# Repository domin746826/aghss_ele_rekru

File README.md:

# aghss_ele_rekru
rekrutacja do ele 2024

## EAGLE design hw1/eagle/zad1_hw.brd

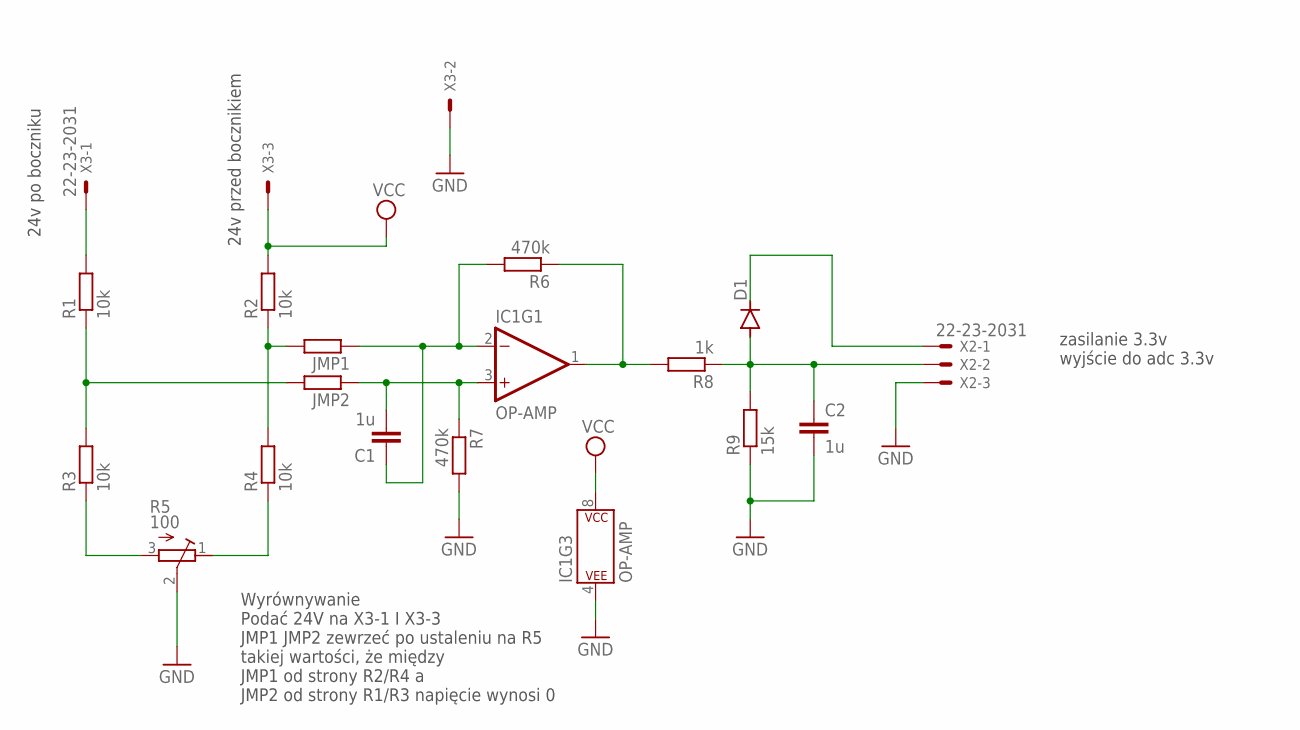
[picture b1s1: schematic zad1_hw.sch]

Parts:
C1, C2: 1u; C1206
D1: DIODE-DO214AC; DO214AC
IC1: OP-AMP; SO08
JMP1, JMP2: 0; R1206
R1, R2, R3, R4: 10k; R1206
R5: 100; RTRIMT93YA
R6, R7: 470k; R1206
R8: 1k; R1206
R9: 15k; R1206
X2, X3: 22-23-2031

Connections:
GND: C2.2, IC1.4 (P$V-), R5.2 (S), R7.2, R9.1, X2.3, X3.2
unnamed: R3.1, R5.3 (A)
unnamed: R4.1, R5.1 (E)
unnamed: JMP1.2, R2.1, R4.2
unnamed: JMP2.2, R1.1, R3.2
unnamed: R1.2, X3.1
unnamed: D1.C, X2.1
unnamed: C1.1, IC1.2 (-IN), JMP1.1, R6.2
unnamed: C1.2, IC1.3 (+IN), JMP2.1, R7.1
unnamed: IC1.1 (OUT), R6.1, R8.2
unnamed: C2.1, D1.A, R8.1, R9.2, X2.2
VCC: IC1.8 (P$V+), R2.2, X3.3

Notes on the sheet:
24v przed bocznikiem
24v po boczniku
zasilanie 3.3v wyjście do adc 3.3v
Wyrównywanie Podać 24V na X3-1 I X3-3 JMP1 JMP2 zewrzeć po ustaleniu na R5 takiej wartości, że między JMP1 od strony R2/R4 a JMP2 od strony R1/R3 napięcie wynosi 0

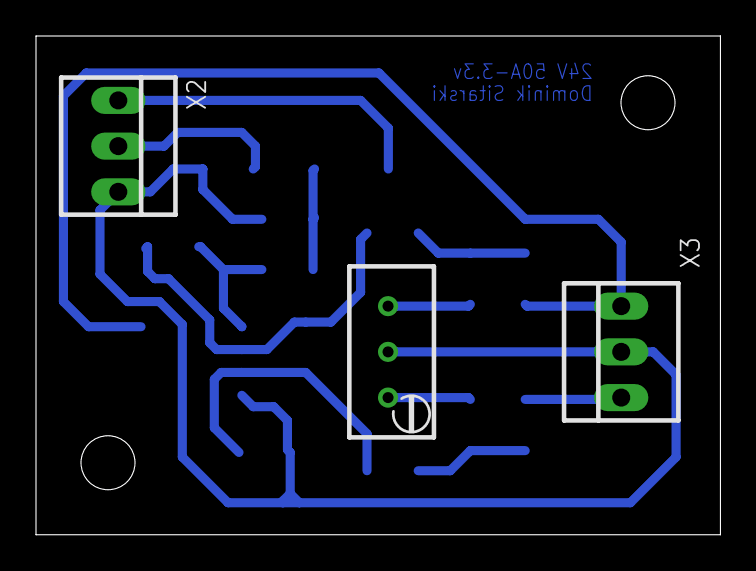
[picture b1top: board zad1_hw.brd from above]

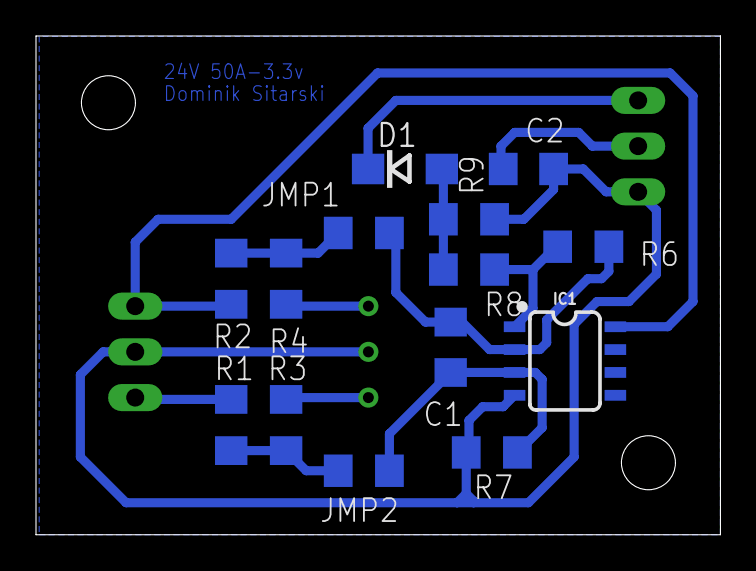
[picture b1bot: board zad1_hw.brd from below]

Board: 2 copper layers, 38.0 x 27.7 mm, 17 parts (14 on the bottom side), 12 nets.

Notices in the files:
parts and their libraries:
SparkFun-IC-Amplifiers: Licensing: Creative Commons ShareAlike 4.0 International - https://creativecommons.org/licenses/by-sa/4.0
